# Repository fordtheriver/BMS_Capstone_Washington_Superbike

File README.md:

# BMS_Capstone_Washington_Superbike
This repository includes firmware, PCB design files and documentation to build the BMS for Washington Superbike. This BMS uses the TI MSP430F5529 microcontroller to interface with the LTC6811-1 Battery Stack Monitor. 

This code is written in C in Code Composer Studio. 

Current firmware is full of bugs and should be debugged by the end of June.

EAGLE PCB design files are included in the EAGLE folder

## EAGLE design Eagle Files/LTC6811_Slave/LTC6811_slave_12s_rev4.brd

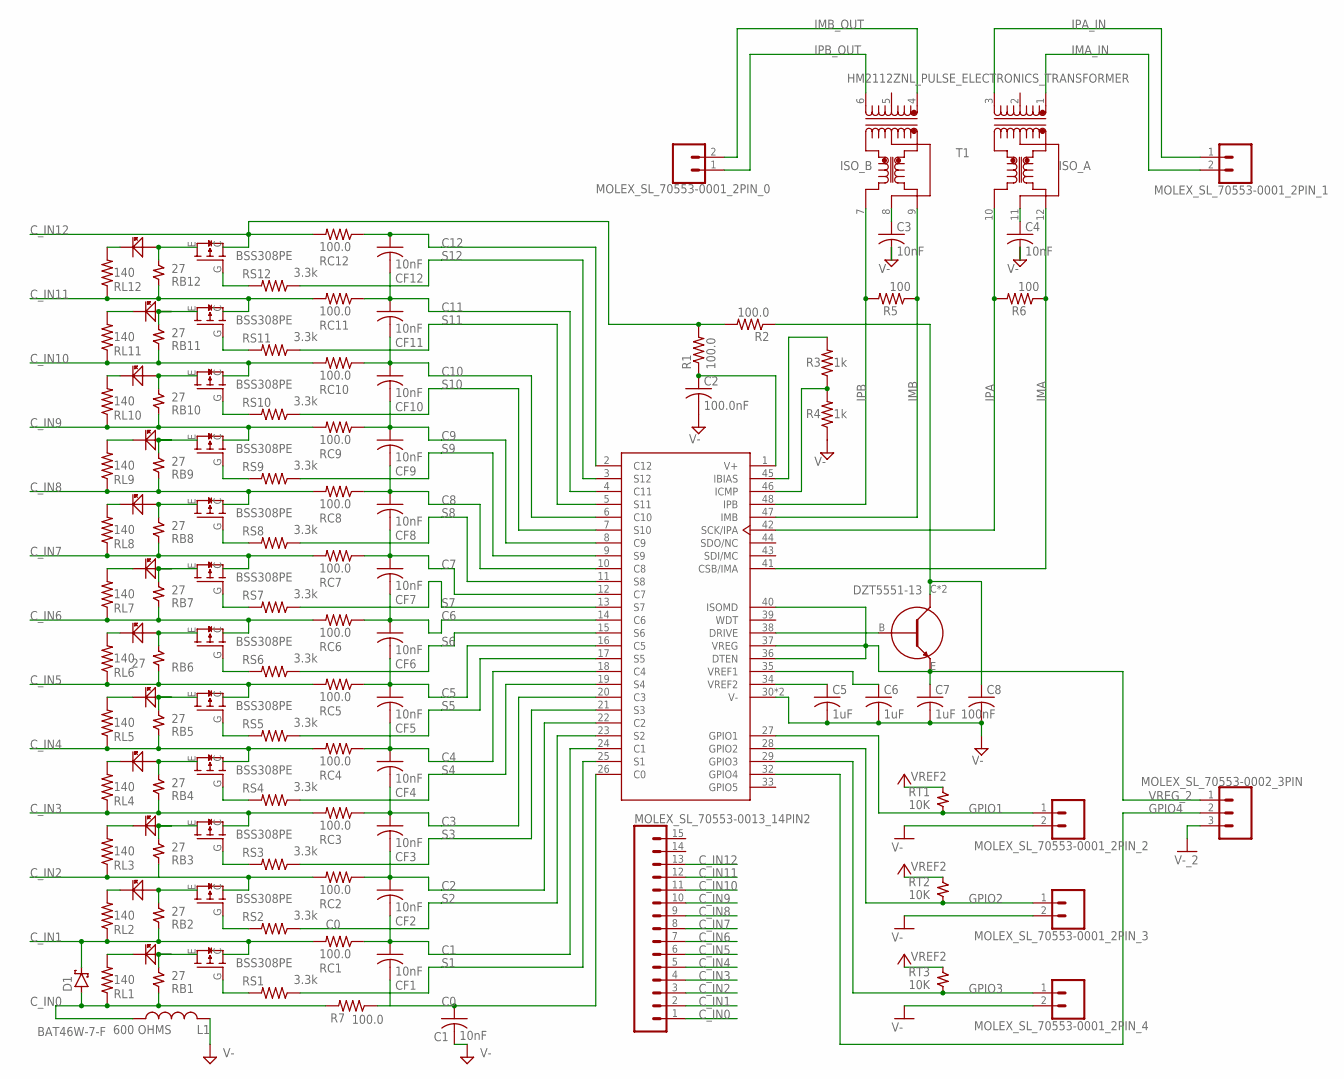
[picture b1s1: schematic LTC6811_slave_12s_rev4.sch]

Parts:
C1, C3, C4: 10nF; C0805
C2: 100.0nF; C0805
C5, C6, C7: 1uF; C0805
C8: 100nF; C0805
CF1, CF2, CF3, CF4, CF5, CF6, CF7, CF8, CF9, CF10, CF11, CF12: 10nF; C0805
D1: BAT46W-7-F; SOD123
L1: 600 OHMS; 0805_COMPONENT
LED1, LED2, LED3, LED4, LED5, LED6, LED7, LED8, LED9, LED10, LED11, LED12: LED_0805; 0805_COMPONENT
MOLEX_SL_70553-0001_2PIN_0, MOLEX_SL_70553-0001_2PIN_1, MOLEX_SL_70553-0001_2PIN_2, MOLEX_SL_70553-0001_2PIN_3, MOLEX_SL_70553-0001_2PIN_4: CONN_02; 1X02
MOLEX_SL_70553-0002_3PIN: CONN_03; 1X03
MOLEX_SL_70553-0013_14PIN2: CONN_15; 1X15
R1, R2, R7: 100.0; R0805
R3, R4: 1k; R0805
R5, R6: 100; R0805
RB1, RB2, RB3, RB4, RB5, RB6, RB7, RB8, RB9, RB10, RB11, RB12: 27; 2817_COMPONENT
RC1, RC2, RC3, RC4, RC5, RC6, RC7, RC8, RC9, RC10, RC11, RC12: 100.0; R0805
RL1, RL2, RL3, RL4, RL5, RL6, RL7, RL8, RL9, RL10, RL11, RL12: 140; R0805
RS1, RS2, RS3, RS4, RS5, RS6, RS7, RS8, RS9, RS10, RS11, RS12: 3.3k; R0805
RT1, RT2, RT3: 10K; 0805_RESISTOR
SW1, SW2, SW3, SW4, SW5, SW6, SW7, SW8, SW9, SW10, SW11, SW12: BSS308PEH6327; SOT23
SW13: DZT5551-13; SOT223-4
U1: LTC6811HG-2#PBF; LTC6811-1
U$3: HM2112ZNL_PULSE_ELECTRONICS_TRANSFORMER; HM2112ZNL_12SMT

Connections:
C0: C1.1, R7.1, U1.26 (C0)
C1: CF1.1, CF2.2, RC1.1, U1.24 (C1)
C2: CF2.1, CF3.2, RC2.1, U1.22 (C2)
C3: CF3.1, CF4.2, RC3.1, U1.20 (C3)
C4: CF4.1, CF5.2, RC4.1, U1.18 (C4)
C5: CF5.1, CF6.2, RC5.1, U1.16 (C5)
C6: CF6.1, CF7.2, RC6.1, U1.14 (C6)
C7: CF7.1, CF8.2, RC7.1, U1.12 (C7)
C8: CF8.1, CF9.2, RC8.1, U1.10 (C8)
C9: CF9.1, CF10.2, RC9.1, U1.8 (C9)
C10: CF10.1, CF11.2, RC10.1, U1.6 (C10)
C11: CF11.1, CF12.2, RC11.1, U1.4 (C11)
C12: CF12.1, RC12.1, U1.2 (C12)
C_IN0: D1.A, L1.1, MOLEX_SL_70553-0013_14PIN2.1, R7.2, RB1.2, RL1.1
C_IN1: D1.C, MOLEX_SL_70553-0013_14PIN2.2, RB2.2, RC1.2, RL2.1, SW1.C
C_IN2: MOLEX_SL_70553-0013_14PIN2.3, RB3.2, RC2.2, RL3.1, SW2.C
C_IN3: MOLEX_SL_70553-0013_14PIN2.4, RB4.2, RC3.2, RL4.1, SW3.C
C_IN4: MOLEX_SL_70553-0013_14PIN2.5, RB5.2, RC4.2, RL5.1, SW4.C
C_IN5: MOLEX_SL_70553-0013_14PIN2.6, RB6.2, RC5.2, RL6.1, SW5.C
C_IN6: MOLEX_SL_70553-0013_14PIN2.7, RB7.2, RC6.2, RL7.1, SW6.C
C_IN7: MOLEX_SL_70553-0013_14PIN2.8, RB8.2, RC7.2, RL8.1, SW7.C
C_IN8: MOLEX_SL_70553-0013_14PIN2.9, RB9.2, RC8.2, RL9.1, SW8.C
C_IN9: MOLEX_SL_70553-0013_14PIN2.10, RB10.2, RC9.2, RL10.1, SW9.C
C_IN10: MOLEX_SL_70553-0013_14PIN2.11, RB11.2, RC10.2, RL11.1, SW10.C
C_IN11: MOLEX_SL_70553-0013_14PIN2.12, RB12.2, RC11.2, RL12.1, SW11.C
C_IN12: MOLEX_SL_70553-0013_14PIN2.13, R1.2, R2.2, RC12.2, SW12.C
DRIVE_2: SW13.B, U1.38 (DRIVE)
GPIO1: MOLEX_SL_70553-0001_2PIN_2.1, RT1.P$2, U1.27 (GPIO1)
GPIO2: MOLEX_SL_70553-0001_2PIN_3.1, RT2.P$2, U1.28 (GPIO2)
GPIO3: MOLEX_SL_70553-0001_2PIN_4.1, RT3.P$2, U1.29 (GPIO3)
GPIO4: MOLEX_SL_70553-0002_3PIN.2, U1.32 (GPIO4)
IBIAS_2: R3.2, U1.45 (IBIAS)
ICMP_2: R3.1, R4.2, U1.46 (ICMP)
IMA: R6.1, U1.41 (CSB/IMA), U$3.12
IMA_IN: MOLEX_SL_70553-0001_2PIN_1.2, U$3.1
IMB: R5.1, U1.47 (IMB), U$3.9
IMB_OUT: MOLEX_SL_70553-0001_2PIN_0.2, U$3.4
IPA: R6.2, U1.42 (SCK/IPA), U$3.10
IPA_IN: MOLEX_SL_70553-0001_2PIN_1.1, U$3.3
IPB: R5.2, U1.48 (IPB), U$3.7
IPB_OUT: MOLEX_SL_70553-0001_2PIN_0.1, U$3.6
unnamed: C2.1, R1.1, U1.1 (V+)
unnamed: C3.1, U$3.8
unnamed: C4.1, U$3.11
unnamed: LED1.2, RB1.1, SW1.E
unnamed: RS1.2, SW1.G (B)
unnamed: LED1.1, RL1.2
unnamed: LED2.2, RB2.1, SW2.E
unnamed: RS2.2, SW2.G (B)
unnamed: LED2.1, RL2.2
unnamed: LED3.2, RB3.1, SW3.E
unnamed: RS3.2, SW3.G (B)
unnamed: LED3.1, RL3.2
unnamed: LED4.2, RB4.1, SW4.E
unnamed: RS4.2, SW4.G (B)
unnamed: LED4.1, RL4.2
unnamed: LED5.2, RB5.1, SW5.E
unnamed: RS5.2, SW5.G (B)
unnamed: LED5.1, RL5.2
unnamed: LED6.2, RB6.1, SW6.E
unnamed: RS6.2, SW6.G (B)
unnamed: LED6.1, RL6.2
unnamed: LED7.2, RB7.1, SW7.E
unnamed: RS7.2, SW7.G (B)
unnamed: LED7.1, RL7.2
unnamed: LED8.2, RB8.1, SW8.E
unnamed: RS8.2, SW8.G (B)
unnamed: LED8.1, RL8.2
unnamed: LED9.2, RB9.1, SW9.E
unnamed: RS9.2, SW9.G (B)
unnamed: LED9.1, RL9.2
unnamed: LED10.2, RB10.1, SW10.E
unnamed: RS10.2, SW10.G (B)
unnamed: LED10.1, RL10.2
unnamed: LED11.2, RB11.1, SW11.E
unnamed: RS11.2, SW11.G (B)
unnamed: LED11.1, RL11.2
unnamed: LED12.2, RB12.1, SW12.E
unnamed: RS12.2, SW12.G (B)
unnamed: LED12.1, RL12.2
S1: RS1.1, U1.25 (S1)
S2: RS2.1, U1.23 (S2)
S3: RS3.1, U1.21 (S3)
S4: RS4.1, U1.19 (S4)
S5: RS5.1, U1.17 (S5)
S6: RS6.1, U1.15 (S6)
S7: RS7.1, U1.13 (S7)
S8: RS8.1, U1.11 (S8)
S9: RS9.1, U1.9 (S9)
S10: RS10.1, U1.7 (S10)
S11: RS11.1, U1.5 (S11)
S12: RS12.1, U1.3 (S12)
V-: C1.2, C2.2, C3.2, C4.2, C5.2, C6.2, C7.2, C8.2, L1.2, MOLEX_SL_70553-0001_2PIN_2.2, MOLEX_SL_70553-0001_2PIN_3.2, MOLEX_SL_70553-0001_2PIN_4.2, MOLEX_SL_70553-0002_3PIN.3, R4.1, U1.30 (V-), U1.31 (V-)
VREF1_C4_2: C6.1, U1.35 (VREF1)
VREF2_C5_2: C5.1, RT1.P$1, RT2.P$1, RT3.P$1, U1.34 (VREF2)
VREG_2: C7.1, MOLEX_SL_70553-0002_3PIN.1, SW13.E, U1.36 (DTEN), U1.37 (VREG), U1.40 (ISOMD)
VREG_CAP_2: C8.1, R2.1, SW13.C, SW13.C@2 (C)

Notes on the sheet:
ISO_B
ISO_A
DZT5551-13

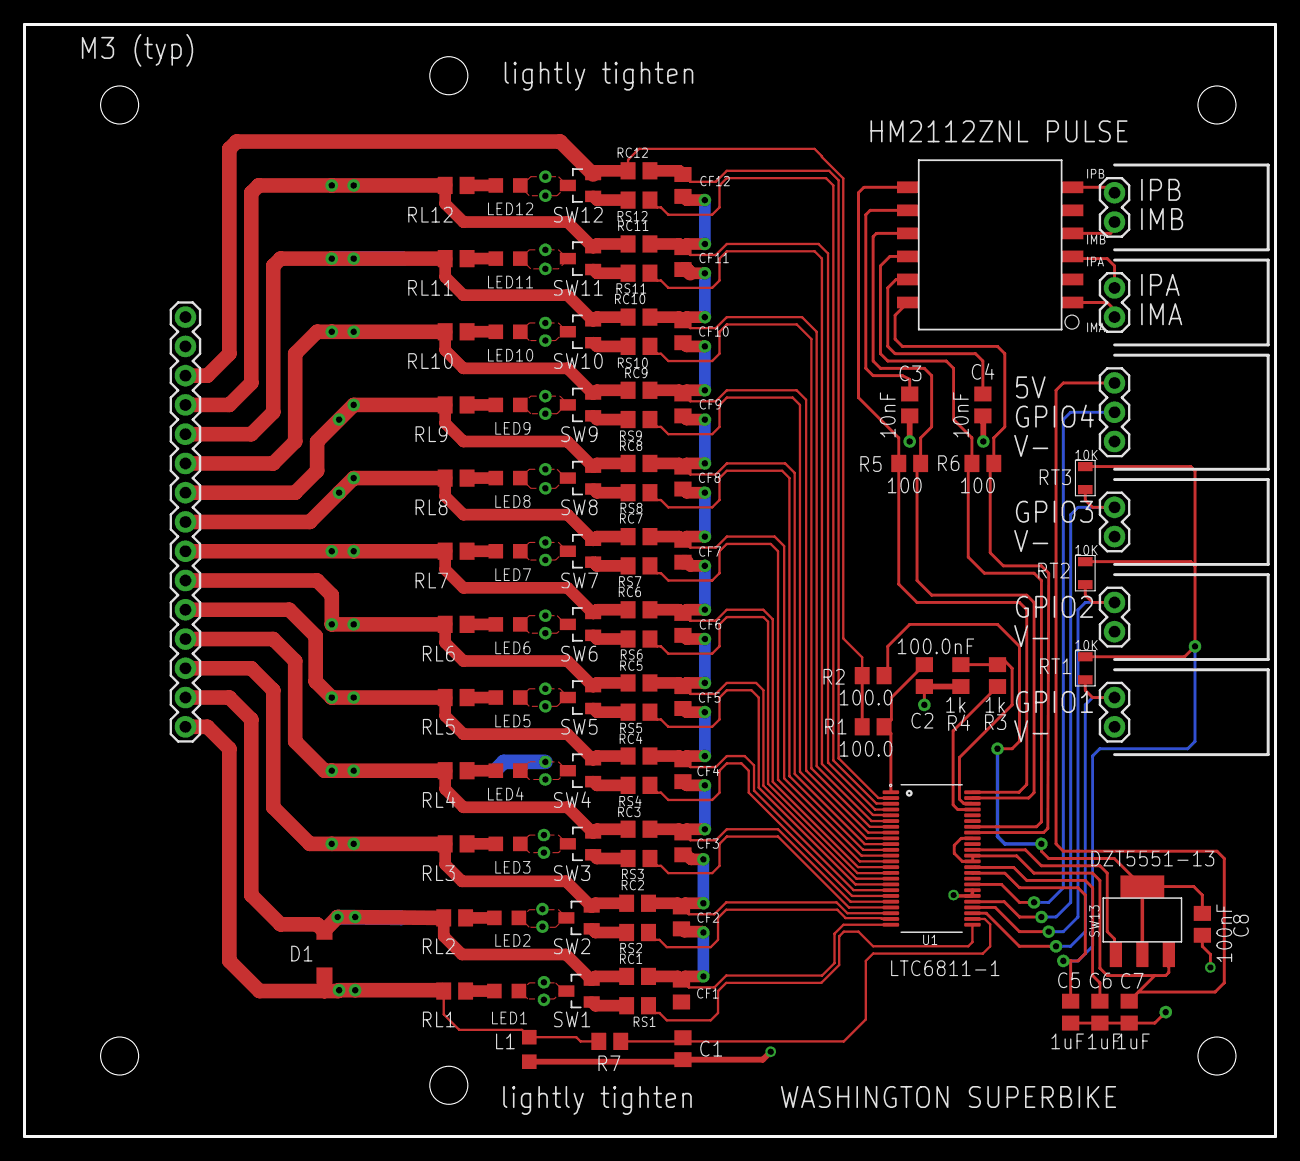
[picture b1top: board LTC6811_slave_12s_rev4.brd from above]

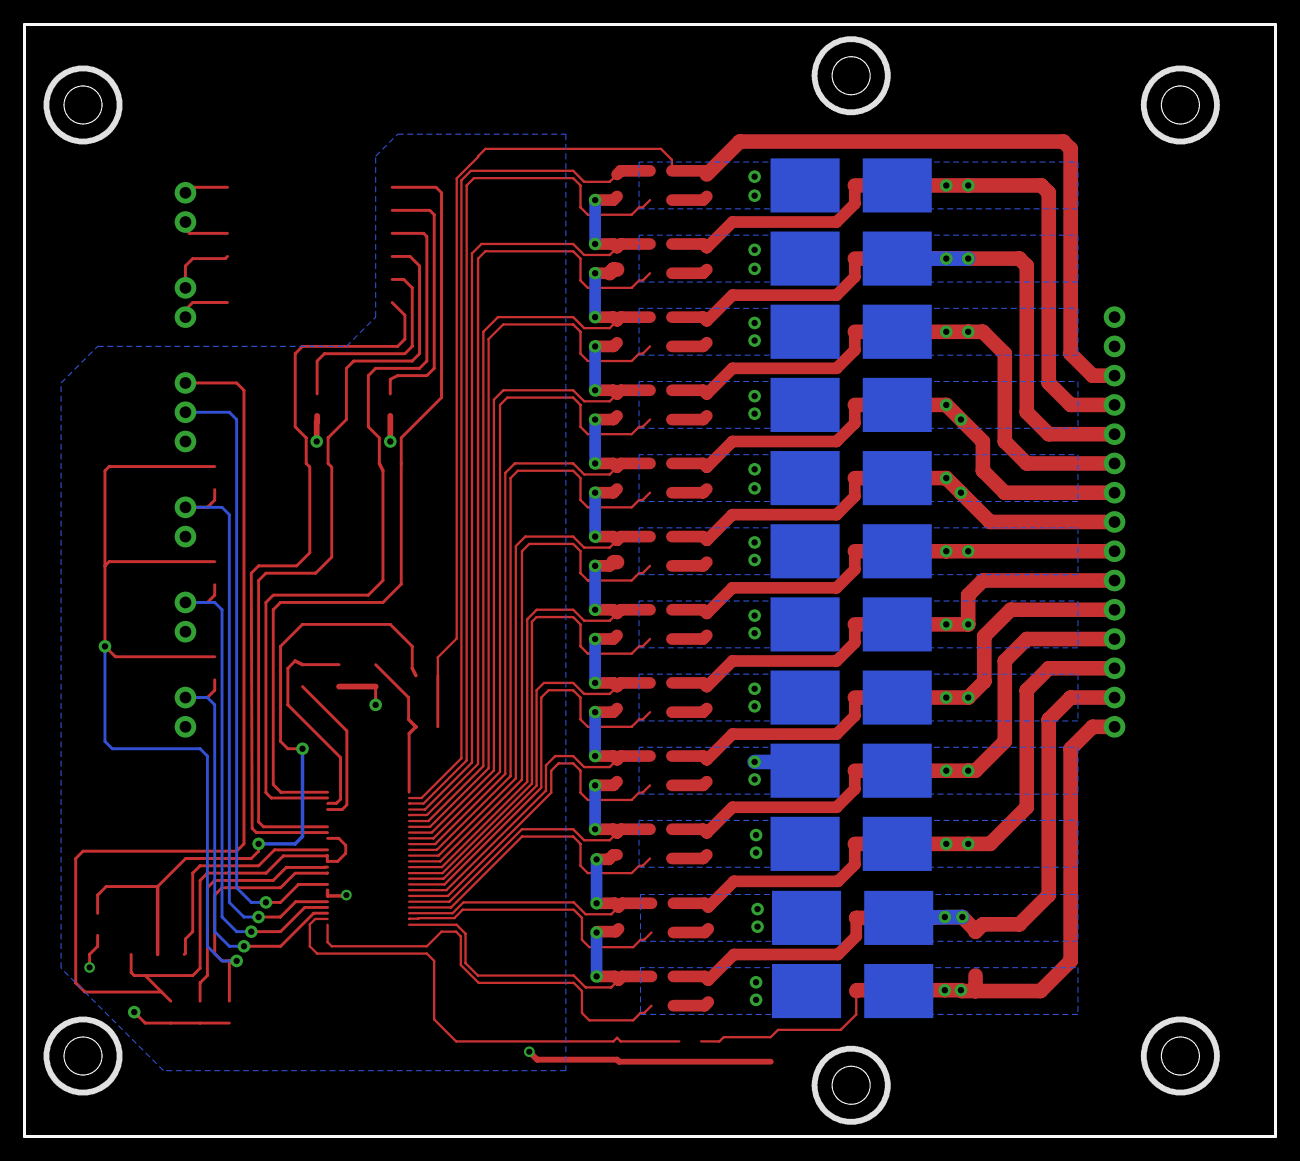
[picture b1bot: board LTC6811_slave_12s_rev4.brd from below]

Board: 2 copper layers, 108.6 x 96.5 mm, 114 parts (12 on the bottom side), 97 nets.

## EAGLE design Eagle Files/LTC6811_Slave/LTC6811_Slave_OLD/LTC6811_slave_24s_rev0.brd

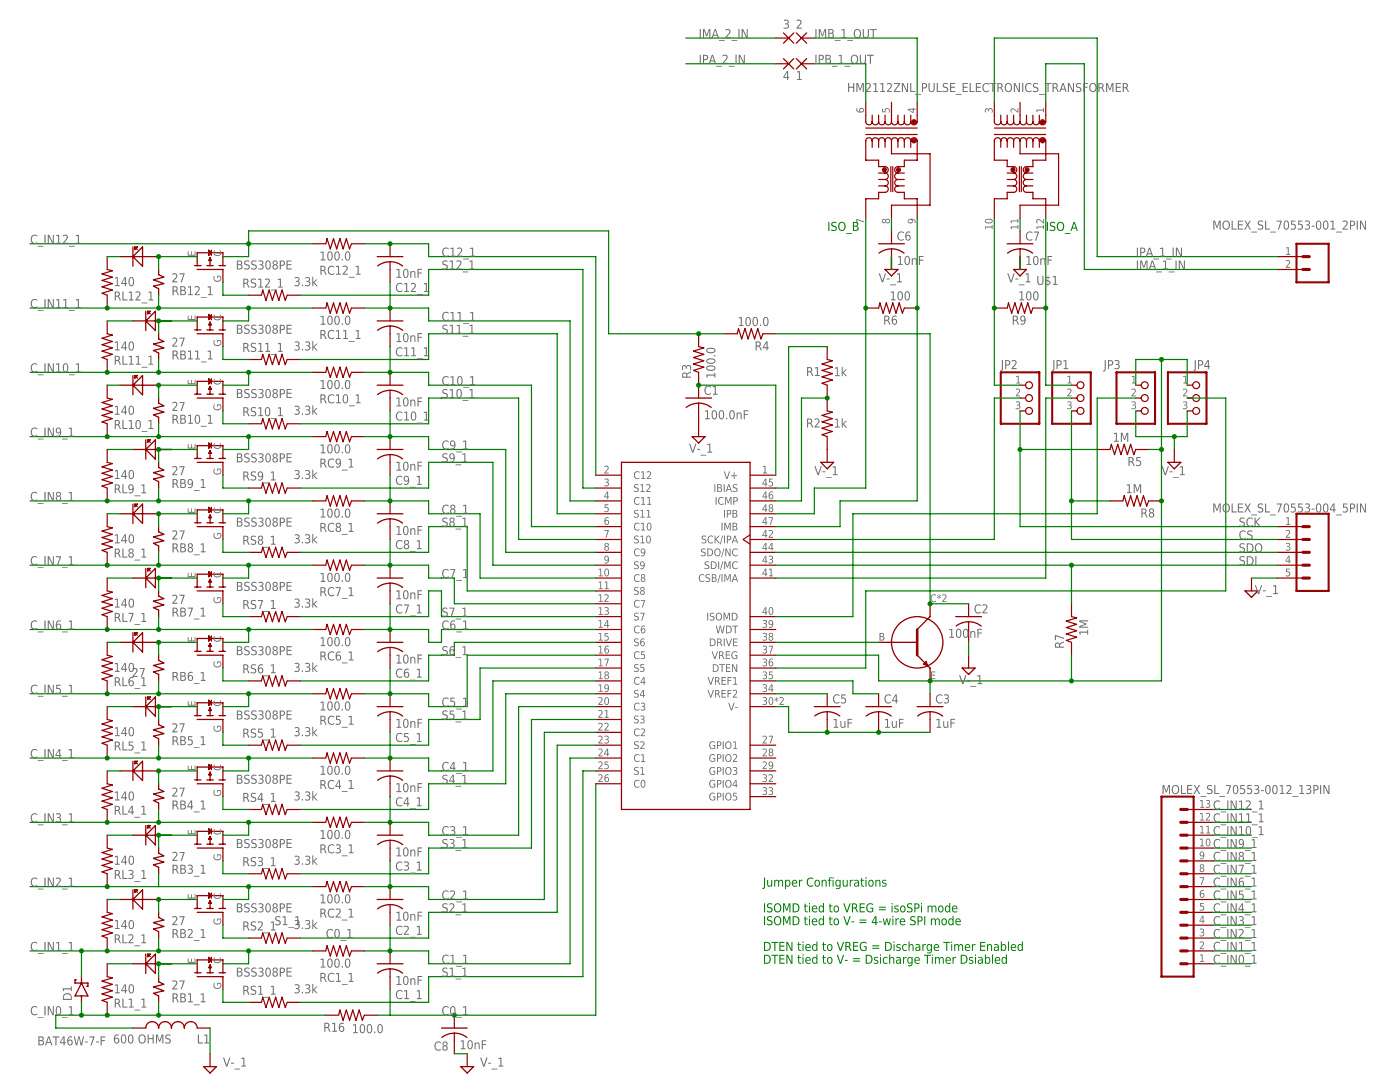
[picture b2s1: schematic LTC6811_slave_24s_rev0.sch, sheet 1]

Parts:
1, 2, 3, 4: WIREPAD2,15/1,0; 2,15/1,0
C1: 100.0nF; C0805
C1_1, C2_1, C3_1, C4_1, C5_1, C6, C6_1, C7, C7_1, C8, C8_1, C9_1, C10_1, C11_1, C12_1: 10nF; C0805
C2: 100nF; C0805
C3, C4, C5: 1uF; C0805
D1: BAT46W-7-F; SOD123
DZT5551-13: DZT5551-13; SOT223-4
JP1, JP2, JP3, JP4: PINHD-1X3; 1X03
L1: 600 OHMS; 0805_COMPONENT
LED1_3, LED1_4, LED1_5, LED1_6, LED1_7, LED1_8, LED1_9, LED1_10, LED1_11, LED1_12, LED1_13, LED1_14: LED_0805; 0805_COMPONENT
MOLEX_SL_70553-001_2PIN: CONN_02; 1X02
MOLEX_SL_70553-004_5PIN: CONN_05; 1X05
MOLEX_SL_70553-0012_13PIN: CONN_13; 1X13
R1, R2: 1k; R0805
R3, R4, R16: 100.0; R0805
R5, R7, R8: 1M; R0805
R6, R9: 100; R0805
RB1_1, RB2_1, RB3_1, RB4_1, RB5_1, RB6_1, RB7_1, RB8_1, RB9_1, RB10_1, RB11_1, RB12_1: 27; 2817_COMPONENT
RC1_1, RC2_1, RC3_1, RC4_1, RC5_1, RC6_1, RC7_1, RC8_1, RC9_1, RC10_1, RC11_1, RC12_1: 100.0; R0805
RL1_1, RL2_1, RL3_1, RL4_1, RL5_1, RL6_1, RL7_1, RL8_1, RL9_1, RL10_1, RL11_1, RL12_1: 140; R0805
RS1_1, RS2_1, RS3_1, RS4_1, RS5_1, RS6_1, RS7_1, RS8_1, RS9_1, RS10_1, RS11_1, RS12_1: 3.3k; R0805
T1_3, T1_4, T1_5, T1_6, T1_7, T1_8, T1_9, T1_10, T1_11, T1_12, T1_13, T1_14: BSS308PEH6327; SOT23
U1: LTC6811HG-2#PBF; LTC6811-1
U$1: HM2112ZNL_PULSE_ELECTRONICS_TRANSFORMER; HM2112ZNL_12SMT

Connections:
C0_1: C8.1, R16.1, U1.26 (C0)
C1_1: C1_1.1, C2_1.2, RC1_1.1, U1.24 (C1)
C2_1: C2_1.1, C3_1.2, RC2_1.1, U1.22 (C2)
C3_1: C3_1.1, C4_1.2, RC3_1.1, U1.20 (C3)
C4_1: C4_1.1, C5_1.2, RC4_1.1, U1.18 (C4)
C5_1: C5_1.1, C6_1.2, RC5_1.1, U1.16 (C5)
C6_1: C6_1.1, C7_1.2, RC6_1.1, U1.14 (C6)
C7_1: C7_1.1, C8_1.2, RC7_1.1, U1.12 (C7)
C8_1: C8_1.1, C9_1.2, RC8_1.1, U1.10 (C8)
C9_1: C9_1.1, C10_1.2, RC9_1.1, U1.8 (C9)
C10_1: C10_1.1, C11_1.2, RC10_1.1, U1.6 (C10)
C11_1: C11_1.1, C12_1.2, RC11_1.1, U1.4 (C11)
C12_1: C12_1.1, RC12_1.1, U1.2 (C12)
CS: JP1.3, MOLEX_SL_70553-004_5PIN.2, R8.2
CS_OR_IMA: JP1.2, U1.41 (CSB/IMA)
C_IN0_1: D1.A, L1.1, MOLEX_SL_70553-0012_13PIN.1, R16.2, RB1_1.2, RL1_1.1
C_IN1_1: D1.C, MOLEX_SL_70553-0012_13PIN.2, RB2_1.2, RC1_1.2, RL2_1.1, T1_3.C
C_IN2_1: MOLEX_SL_70553-0012_13PIN.3, RB3_1.2, RC2_1.2, RL3_1.1, T1_4.C
C_IN3_1: MOLEX_SL_70553-0012_13PIN.4, RB4_1.2, RC3_1.2, RL4_1.1, T1_7.C
C_IN4_1: MOLEX_SL_70553-0012_13PIN.5, RB5_1.2, RC4_1.2, RL5_1.1, T1_8.C
C_IN5_1: MOLEX_SL_70553-0012_13PIN.6, RB6_1.2, RC5_1.2, RL6_1.1, T1_5.C
C_IN6_1: MOLEX_SL_70553-0012_13PIN.7, RB7_1.2, RC6_1.2, RL7_1.1, T1_6.C
C_IN7_1: MOLEX_SL_70553-0012_13PIN.8, RB8_1.2, RC7_1.2, RL8_1.1, T1_9.C
C_IN8_1: MOLEX_SL_70553-0012_13PIN.9, RB9_1.2, RC8_1.2, RL9_1.1, T1_10.C
C_IN9_1: MOLEX_SL_70553-0012_13PIN.10, RB10_1.2, RC9_1.2, RL10_1.1, T1_11.C
C_IN10_1: MOLEX_SL_70553-0012_13PIN.11, RB11_1.2, RC10_1.2, RL11_1.1, T1_12.C
C_IN11_1: MOLEX_SL_70553-0012_13PIN.12, RB12_1.2, RC11_1.2, RL12_1.1, T1_13.C
C_IN12_1: MOLEX_SL_70553-0012_13PIN.13, R3.2, R4.2, RC12_1.2, T1_14.C
DRIVE: DZT5551-13.B, U1.38 (DRIVE)
DTEN: JP4.2, U1.36 (DTEN)
IBIAS: R1.2, U1.45 (IBIAS)
ICMP: R1.1, R2.2, U1.46 (ICMP)
IMA_1_IN: MOLEX_SL_70553-001_2PIN.2, U$1.1
IMA_2_IN: 3.1; also elsewhere on the board
IMB: R6.1, U1.47 (IMB), U$1.9
IMB_1_OUT: 2.1, U$1.4
IPA_1_IN: MOLEX_SL_70553-001_2PIN.1, U$1.3
IPA_2_IN: 4.1; also elsewhere on the board
IPB: R6.2, U1.48 (IPB), U$1.7
IPB_1_OUT: 1.1, U$1.6
ISOMD: JP3.2, U1.40 (ISOMD)
unnamed: C6.1, U$1.8
unnamed: C1.1, R3.1, U1.1 (V+)
unnamed: JP2.1, R9.2, U$1.10
unnamed: JP1.1, R9.1, U$1.12
unnamed: C7.1, U$1.11
unnamed: LED1_11.2, RB9_1.1, T1_11.E
unnamed: RS9_1.2, T1_11.G (B)
unnamed: LED1_11.1, RL9_1.2
unnamed: LED1_12.2, RB10_1.1, T1_12.E
unnamed: RS10_1.2, T1_12.G (B)
unnamed: LED1_12.1, RL10_1.2
unnamed: LED1_13.2, RB11_1.1, T1_13.E
unnamed: LED1_3.2, RB1_1.1, T1_3.E
unnamed: RS1_1.2, T1_3.G (B)
unnamed: LED1_3.1, RL1_1.2
unnamed: LED1_4.2, RB2_1.1, T1_4.E
unnamed: RS2_1.2, T1_4.G (B)
unnamed: LED1_4.1, RL2_1.2
unnamed: LED1_5.2, RB5_1.1, T1_5.E
unnamed: RS5_1.2, T1_5.G (B)
unnamed: LED1_5.1, RL5_1.2
unnamed: LED1_6.2, RB6_1.1, T1_6.E
unnamed: RS6_1.2, T1_6.G (B)
unnamed: LED1_6.1, RL6_1.2
unnamed: LED1_9.2, RB7_1.1, T1_9.E
unnamed: LED1_7.2, RB3_1.1, T1_7.E
unnamed: RS3_1.2, T1_7.G (B)
unnamed: LED1_7.1, RL3_1.2
unnamed: LED1_8.2, RB4_1.1, T1_8.E
unnamed: RS4_1.2, T1_8.G (B)
unnamed: LED1_8.1, RL4_1.2
unnamed: RS11_1.2, T1_13.G (B)
unnamed: RS7_1.2, T1_9.G (B)
unnamed: LED1_9.1, RL7_1.2
unnamed: LED1_10.2, RB8_1.1, T1_10.E
unnamed: RS8_1.2, T1_10.G (B)
unnamed: LED1_10.1, RL8_1.2
unnamed: LED1_13.1, RL11_1.2
unnamed: LED1_14.2, RB12_1.1, T1_14.E
unnamed: RS12_1.2, T1_14.G (B)
unnamed: LED1_14.1, RL12_1.2
S1_1: RS1_1.1, U1.25 (S1)
S2_1: RS2_1.1, U1.23 (S2)
S3_1: RS3_1.1, U1.21 (S3)
S4_1: RS4_1.1, U1.19 (S4)
S5_1: RS5_1.1, U1.17 (S5)
S6_1: RS6_1.1, U1.15 (S6)
S7_1: RS7_1.1, U1.13 (S7)
S8_1: RS8_1.1, U1.11 (S8)
S9_1: RS9_1.1, U1.9 (S9)
S10_1: RS10_1.1, U1.7 (S10)
S11_1: RS11_1.1, U1.5 (S11)
S12_1: RS12_1.1, U1.3 (S12)
SCK: JP2.3, MOLEX_SL_70553-004_5PIN.1, R5.2
SCK_OR_IPA: JP2.2, U1.42 (SCK/IPA)
SDI: MOLEX_SL_70553-004_5PIN.4, R7.2, U1.43 (SDI/MC)
SDO: MOLEX_SL_70553-004_5PIN.3, U1.44 (SDO/NC)
V-_1: C1.2, C2.2, C3.2, C4.2, C5.2, C6.2, C7.2, C8.2, JP3.3, JP4.3, L1.2, MOLEX_SL_70553-004_5PIN.5, R2.1, U1.30 (V-), U1.31 (V-)
VREF1_C4: C4.1, U1.35 (VREF1)
VREF2_C5: C5.1, U1.34 (VREF2)
VREG: C3.1, DZT5551-13.E, JP3.1, JP4.1, R5.1, R7.1, R8.1, U1.37 (VREG)
VREG_CAP: C2.1, DZT5551-13.C, DZT5551-13.C@2 (C), R4.1

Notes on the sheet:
ISO_B
ISO_A
ISOMD tied to VREG = isoSPi mode
ISOMD tied to V- = 4-wire SPI mode
DTEN tied to VREG = Discharge Timer Enabled
DTEN tied to V- = Dsicharge Timer Dsiabled
Jumper Configurations

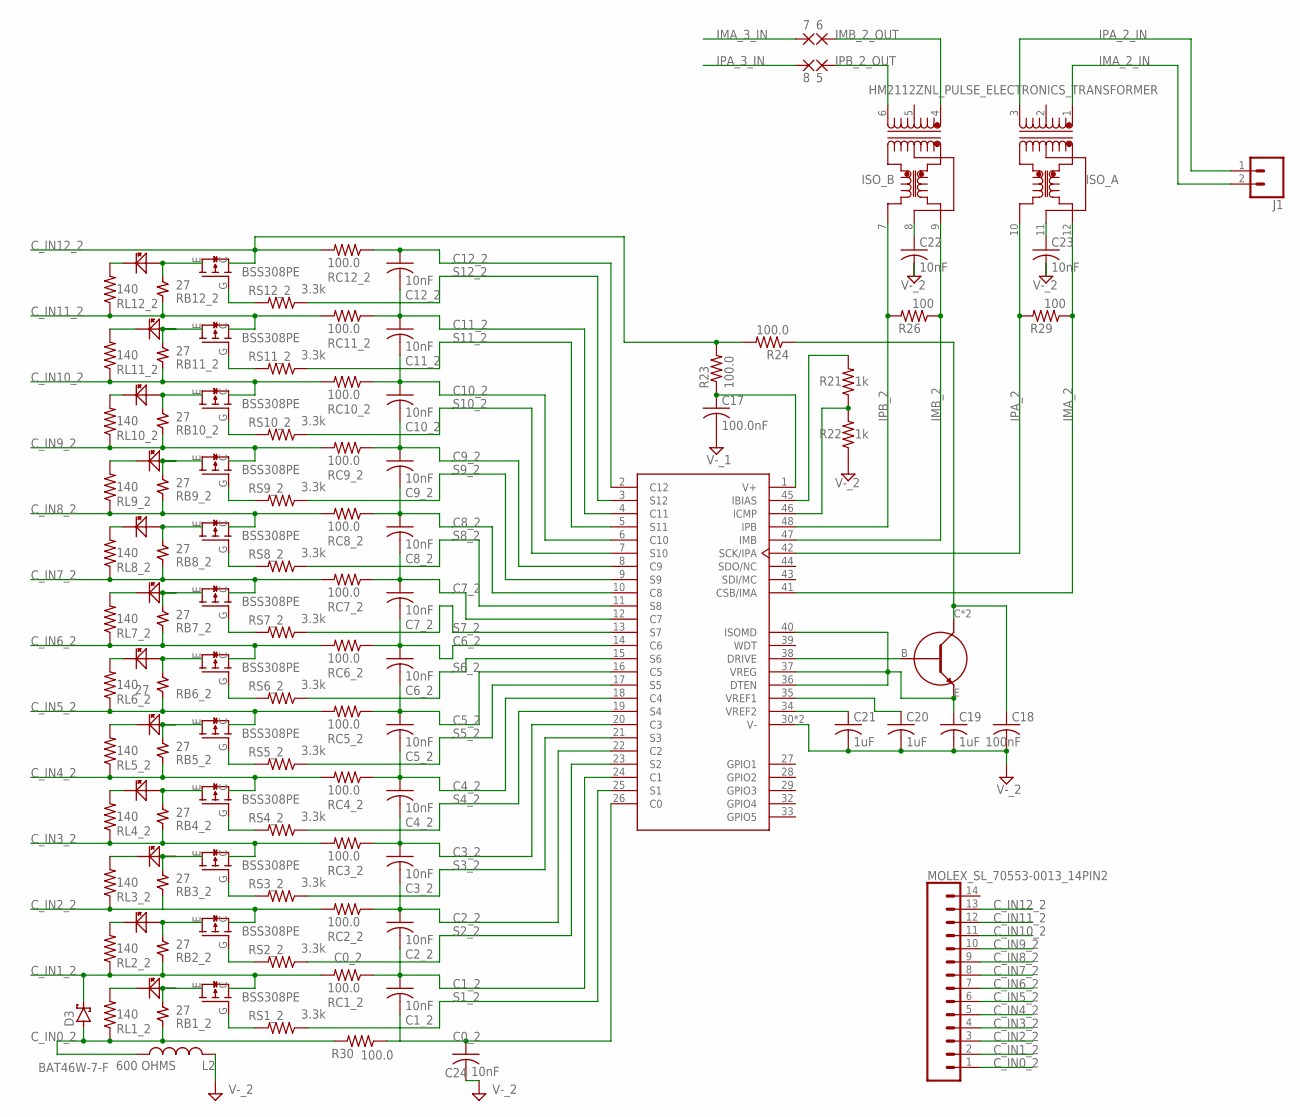
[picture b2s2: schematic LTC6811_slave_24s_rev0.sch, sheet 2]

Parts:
5, 6, 7, 8: WIREPAD2,15/1,0; 2,15/1,0
C1_2, C2_2, C3_2, C4_2, C5_2, C6_2, C7_2, C8_2, C9_2, C10_2, C11_2, C12_2, C22, C23, C24: 10nF; C0805
C17: 100.0nF; C0805
C18: 100nF; C0805
C19, C20, C21: 1uF; C0805
D3: BAT46W-7-F; SOD123
DZT5551-2: DZT5551-13; SOT223-4
J1: CONN_02; 1X02
L2: 600 OHMS; 0805_COMPONENT
LED1_25, LED1_26, LED1_27, LED1_28, LED1_29, LED1_30, LED1_31, LED1_32, LED1_33, LED1_34, LED1_35, LED1_36: LED_0805; 0805_COMPONENT
MOLEX_SL_70553-0013_14PIN2: CONN_14; 1X14
R21, R22: 1k; R0805
R23, R24, R30: 100.0; R0805
R26, R29: 100; R0805
RB1_2, RB2_2, RB3_2, RB4_2, RB5_2, RB6_2, RB7_2, RB8_2, RB9_2, RB10_2, RB11_2, RB12_2: 27; 2817_COMPONENT
RC1_2, RC2_2, RC3_2, RC4_2, RC5_2, RC6_2, RC7_2, RC8_2, RC9_2, RC10_2, RC11_2, RC12_2: 100.0; R0805
RL1_2, RL2_2, RL3_2, RL4_2, RL5_2, RL6_2, RL7_2, RL8_2, RL9_2, RL10_2, RL11_2, RL12_2: 140; R0805
RS1_2, RS2_2, RS3_2, RS4_2, RS5_2, RS6_2, RS7_2, RS8_2, RS9_2, RS10_2, RS11_2, RS12_2: 3.3k; R0805
T1_25, T1_26, T1_27, T1_28, T1_29, T1_30, T1_31, T1_32, T1_33, T1_34, T1_35, T1_36: BSS308PEH6327; SOT23
U3: LTC6811HG-2#PBF; LTC6811-1
U$3: HM2112ZNL_PULSE_ELECTRONICS_TRANSFORMER; HM2112ZNL_12SMT

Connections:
C0_2: C24.1, R30.1, U3.26 (C0)
C1_2: C1_2.1, C2_2.2, RC1_2.1, U3.24 (C1)
C2_2: C2_2.1, C3_2.2, RC2_2.1, U3.22 (C2)
C3_2: C3_2.1, C4_2.2, RC3_2.1, U3.20 (C3)
C4_2: C4_2.1, C5_2.2, RC4_2.1, U3.18 (C4)
C5_2: C5_2.1, C6_2.2, RC5_2.1, U3.16 (C5)
C6_2: C6_2.1, C7_2.2, RC6_2.1, U3.14 (C6)
C7_2: C7_2.1, C8_2.2, RC7_2.1, U3.12 (C7)
C8_2: C8_2.1, C9_2.2, RC8_2.1, U3.10 (C8)
C9_2: C9_2.1, C10_2.2, RC9_2.1, U3.8 (C9)
C10_2: C10_2.1, C11_2.2, RC10_2.1, U3.6 (C10)
C11_2: C11_2.1, C12_2.2, RC11_2.1, U3.4 (C11)
C12_2: C12_2.1, RC12_2.1, U3.2 (C12)
C_IN0_2: D3.A, L2.1, MOLEX_SL_70553-0013_14PIN2.1, R30.2, RB1_2.2, RL1_2.1
C_IN1_2: D3.C, MOLEX_SL_70553-0013_14PIN2.2, RB2_2.2, RC1_2.2, RL2_2.1, T1_25.C
C_IN2_2: MOLEX_SL_70553-0013_14PIN2.3, RB3_2.2, RC2_2.2, RL3_2.1, T1_26.C
C_IN3_2: MOLEX_SL_70553-0013_14PIN2.4, RB4_2.2, RC3_2.2, RL4_2.1, T1_27.C
C_IN4_2: MOLEX_SL_70553-0013_14PIN2.5, RB5_2.2, RC4_2.2, RL5_2.1, T1_28.C
C_IN5_2: MOLEX_SL_70553-0013_14PIN2.6, RB6_2.2, RC5_2.2, RL6_2.1, T1_29.C
C_IN6_2: MOLEX_SL_70553-0013_14PIN2.7, RB7_2.2, RC6_2.2, RL7_2.1, T1_30.C
C_IN7_2: MOLEX_SL_70553-0013_14PIN2.8, RB8_2.2, RC7_2.2, RL8_2.1, T1_31.C
C_IN8_2: MOLEX_SL_70553-0013_14PIN2.9, RB9_2.2, RC8_2.2, RL9_2.1, T1_32.C
C_IN9_2: MOLEX_SL_70553-0013_14PIN2.10, RB10_2.2, RC9_2.2, RL10_2.1, T1_33.C
C_IN10_2: MOLEX_SL_70553-0013_14PIN2.11, RB11_2.2, RC10_2.2, RL11_2.1, T1_34.C
C_IN11_2: MOLEX_SL_70553-0013_14PIN2.12, RB12_2.2, RC11_2.2, RL12_2.1, T1_35.C
C_IN12_2: MOLEX_SL_70553-0013_14PIN2.13, R23.2, R24.2, RC12_2.2, T1_36.C
DRIVE_2: DZT5551-2.B, U3.38 (DRIVE)
IBIAS_2: R21.2, U3.45 (IBIAS)
ICMP_2: R21.1, R22.2, U3.46 (ICMP)
IMA_2: R29.1, U3.41 (CSB/IMA), U$3.12
IMA_2_IN: J1.2, U$3.1; also elsewhere on the board
IMA_3_IN: 7.1
IMB_2: R26.1, U3.47 (IMB), U$3.9
IMB_2_OUT: 6.1, U$3.4
IPA_2: R29.2, U3.42 (SCK/IPA), U$3.10
IPA_2_IN: J1.1, U$3.3; also elsewhere on the board
IPA_3_IN: 8.1
IPB_2: R26.2, U3.48 (IPB), U$3.7
IPB_2_OUT: 5.1, U$3.6
unnamed: C17.1, R23.1, U3.1 (V+)
unnamed: C22.1, U$3.8
unnamed: C23.1, U$3.11
unnamed: LED1_25.2, RB1_2.1, T1_25.E
unnamed: RS1_2.2, T1_25.G (B)
unnamed: LED1_25.1, RL1_2.2
unnamed: LED1_26.2, RB2_2.1, T1_26.E
unnamed: RS2_2.2, T1_26.G (B)
unnamed: LED1_26.1, RL2_2.2
unnamed: LED1_27.2, RB3_2.1, T1_27.E
unnamed: RS3_2.2, T1_27.G (B)
unnamed: LED1_27.1, RL3_2.2
unnamed: LED1_28.2, RB4_2.1, T1_28.E
unnamed: RS4_2.2, T1_28.G (B)
unnamed: LED1_28.1, RL4_2.2
unnamed: LED1_29.2, RB5_2.1, T1_29.E
unnamed: RS5_2.2, T1_29.G (B)
unnamed: LED1_29.1, RL5_2.2
unnamed: LED1_30.2, RB6_2.1, T1_30.E
unnamed: RS6_2.2, T1_30.G (B)
unnamed: LED1_30.1, RL6_2.2
unnamed: LED1_31.2, RB7_2.1, T1_31.E
unnamed: RS7_2.2, T1_31.G (B)
unnamed: LED1_31.1, RL7_2.2
unnamed: LED1_32.2, RB8_2.1, T1_32.E
unnamed: RS8_2.2, T1_32.G (B)
unnamed: LED1_32.1, RL8_2.2
unnamed: LED1_33.2, RB9_2.1, T1_33.E
unnamed: RS9_2.2, T1_33.G (B)
unnamed: LED1_33.1, RL9_2.2
unnamed: LED1_34.2, RB10_2.1, T1_34.E
unnamed: RS10_2.2, T1_34.G (B)
unnamed: LED1_34.1, RL10_2.2
unnamed: LED1_35.2, RB11_2.1, T1_35.E
unnamed: RS11_2.2, T1_35.G (B)
unnamed: LED1_35.1, RL11_2.2
unnamed: LED1_36.2, RB12_2.1, T1_36.E
unnamed: RS12_2.2, T1_36.G (B)
unnamed: LED1_36.1, RL12_2.2
S1_2: RS1_2.1, U3.25 (S1)
S2_2: RS2_2.1, U3.23 (S2)
S3_2: RS3_2.1, U3.21 (S3)
S4_2: RS4_2.1, U3.19 (S4)
S5_2: RS5_2.1, U3.17 (S5)
S6_2: RS6_2.1, U3.15 (S6)
S7_2: RS7_2.1, U3.13 (S7)
S8_2: RS8_2.1, U3.11 (S8)
S9_2: RS9_2.1, U3.9 (S9)
S10_2: RS10_2.1, U3.7 (S10)
S11_2: RS11_2.1, U3.5 (S11)
S12_2: RS12_2.1, U3.3 (S12)
V-_2: C17.2, C18.2, C19.2, C20.2, C21.2, C22.2, C23.2, C24.2, L2.2, R22.1, U3.30 (V-), U3.31 (V-)
VREF1_C4_2: C20.1, U3.35 (VREF1)
VREF2_C5_2: C21.1, U3.34 (VREF2)
VREG_2: C19.1, DZT5551-2.E, U3.36 (DTEN), U3.37 (VREG), U3.40 (ISOMD)
VREG_CAP_2: C18.1, DZT5551-2.C, DZT5551-2.C@2 (C), R24.1

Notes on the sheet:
ISO_B
ISO_A

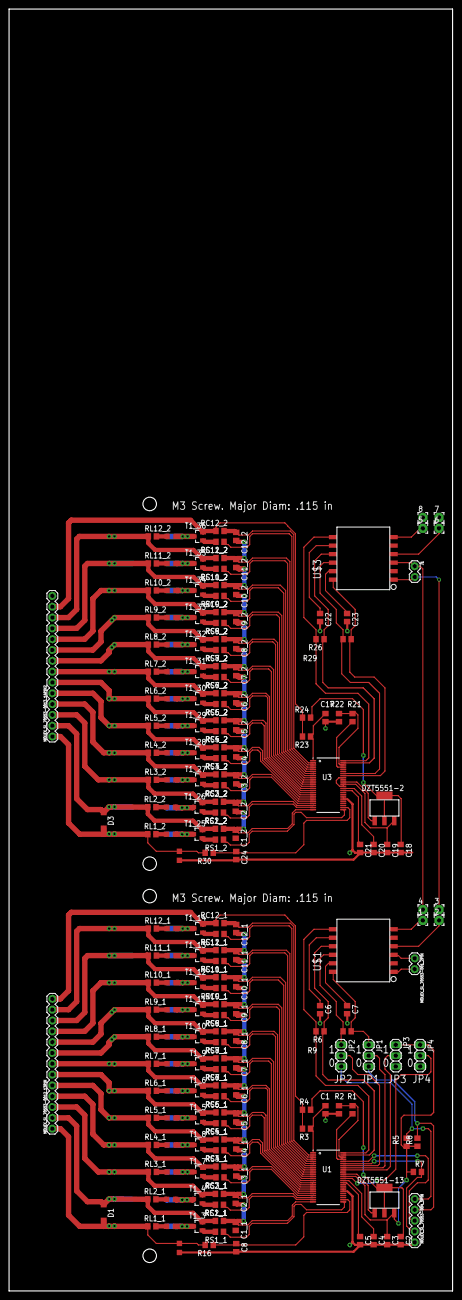
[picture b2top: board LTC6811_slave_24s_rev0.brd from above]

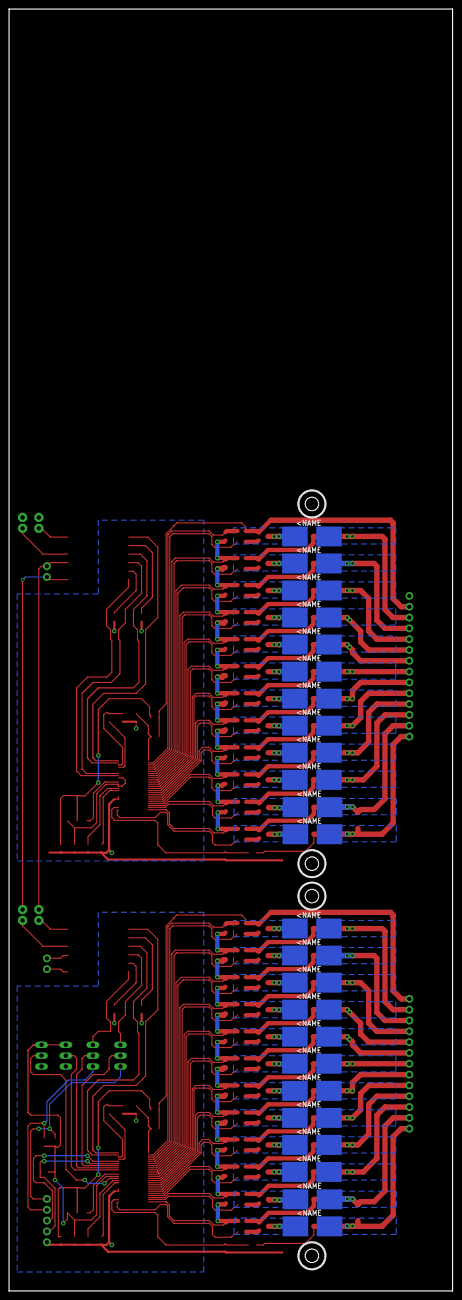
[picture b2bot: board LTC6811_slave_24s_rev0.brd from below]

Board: 2 copper layers, 104.1 x 301.0 mm, 228 parts (24 on the bottom side), 194 nets.

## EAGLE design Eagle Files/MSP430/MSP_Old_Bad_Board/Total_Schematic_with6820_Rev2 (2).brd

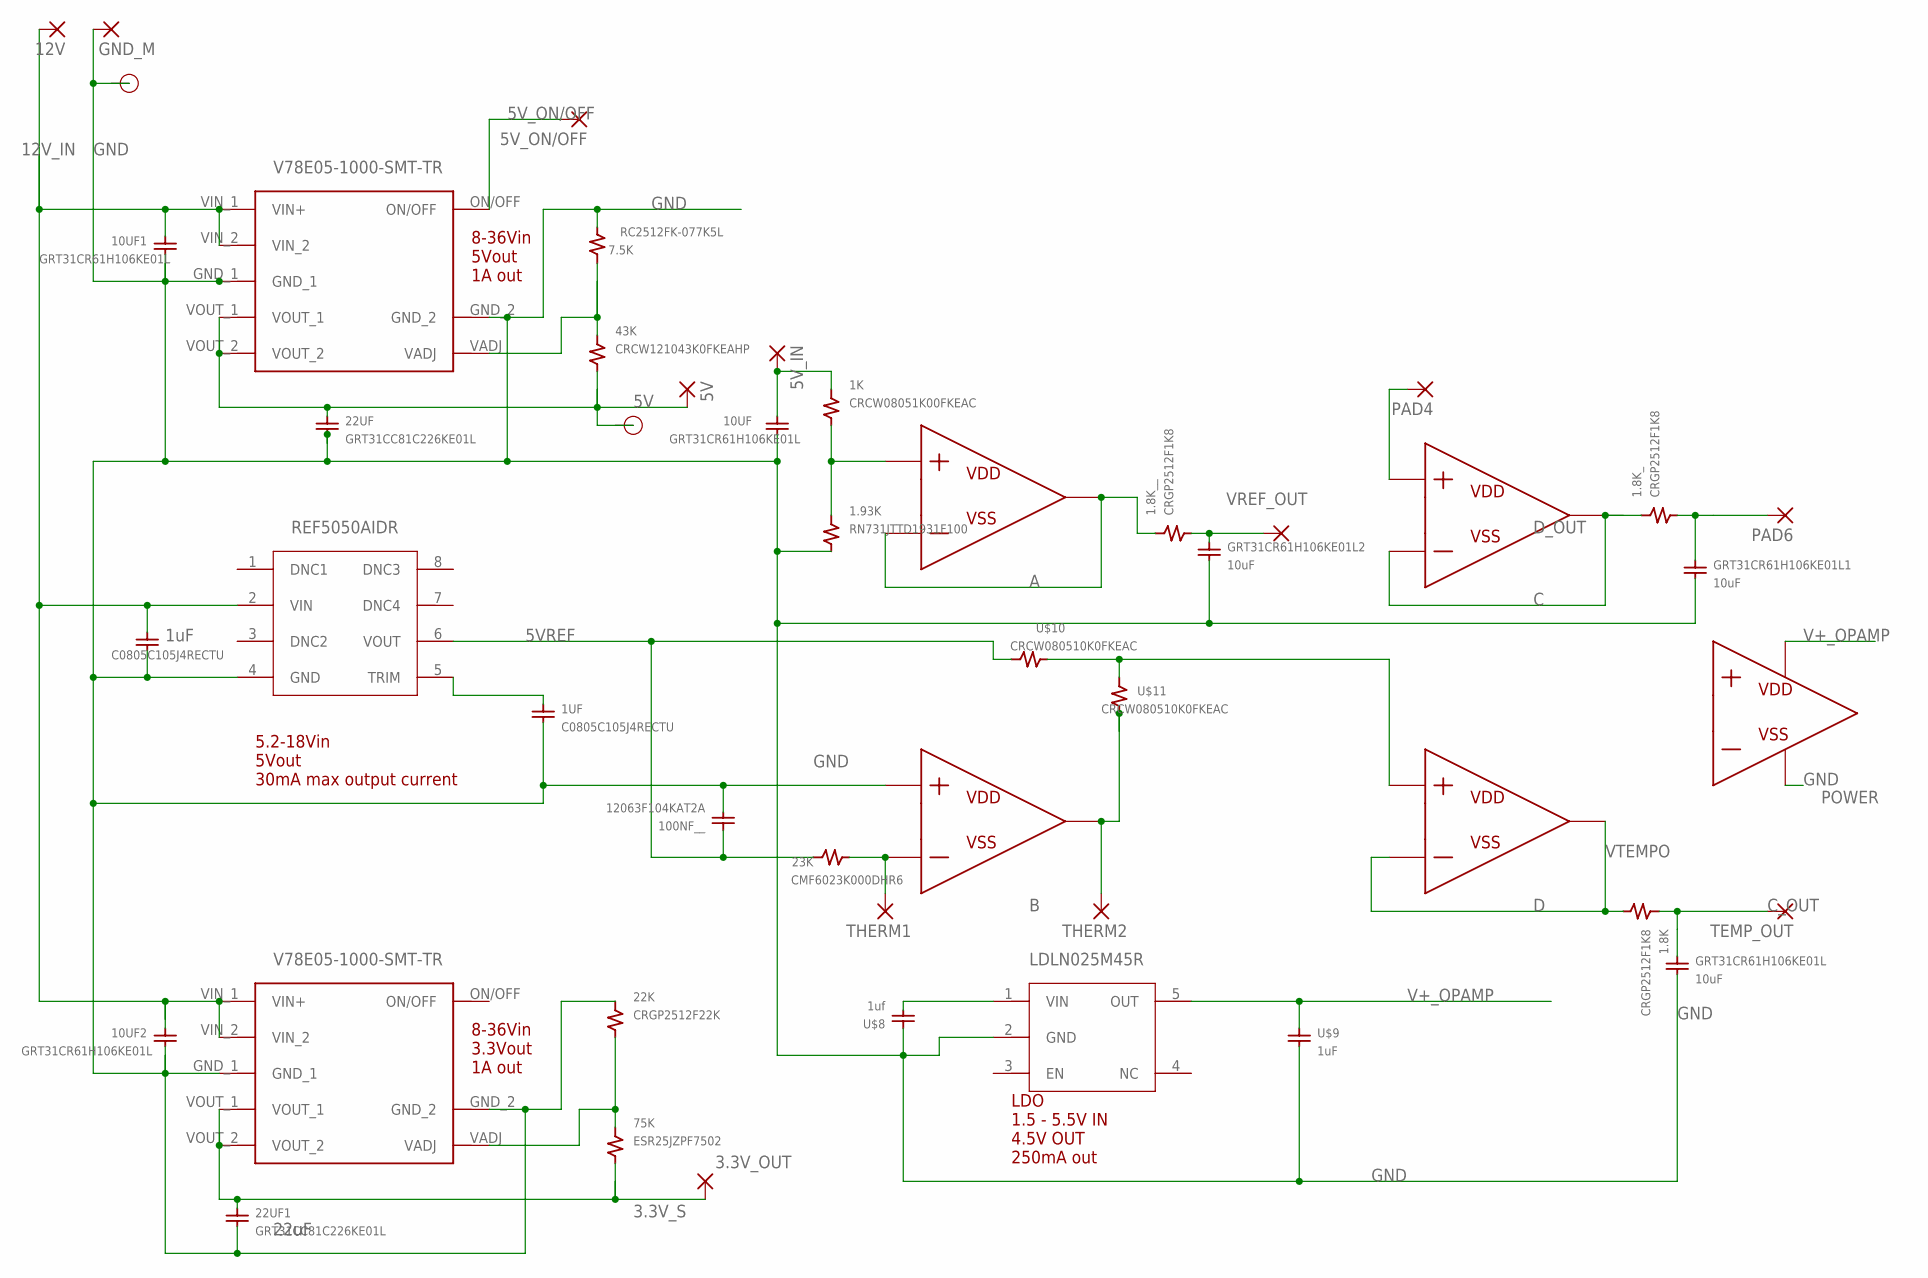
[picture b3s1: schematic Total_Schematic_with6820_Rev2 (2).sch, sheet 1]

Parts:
1.8K, 1.8K_, 1.8K__: CRGP2512F1K8
1.93K: RN731JTTD1931F100
1K: CRCW08051K00FKEAC
1UF: C0805C105J4RECTU
3.3V_OUT, 5V_ON/OFF: 2,15/1,0
5V, 5V_IN, 12V: WIREPAD2,54/1,0; 2,54/1,0
5V_2: HEADER_PIN_2.15/1.0; 2,15/1,0
7.5K: RC2512FK-077K5L
10UF, 10UF1, 10UF2: GRT31CR61H106KE01L
22K: CRGP2512F22K
22UF, 22UF1: GRT31CC81C226KE01L
23K: CMF6023K000DHR6
43K: CRCW121043K0FKEAHP
75K: ESR25JZPF7502
100NF__: 12063F104KAT2A
GND2: HEADER_PIN_2.15/1.0; 2,15/1,0
GND_M: WIREPAD2,54/1,0; 2,54/1,0
GRT31CR61H106KE01L, GRT31CR61H106KE01L1, GRT31CR61H106KE01L2: 10uF; GRT31CR61H106KE01L
PAD4: WIREPAD2,54/1,0; 2,54/1,0
PAD6: 2,15/1,0
TEMP_OUT: 2,15/1,0
THERM1: WIREPAD2,54/1,0; 2,54/1,0
THERM2: 2,15/1,0
U$1: V78E05-SMT-TR; V78E05-1000-SMT-TR
U$2: V78E03-SMT-TR; V78E03-1000-SMT-TR
U$3: REF5050AIDRREF5050AIDR; SO08
U$4: LDLN025M45R
U$5: C0805C105J4RECTU
U$8: 1uf; C0805C105J4RECTU
U$9: 1uF; C0805C105J4RECTU
U$10, U$11: CRCW080510K0FKEAC
U$12: TSV914AIDR
VREF_OUT: 2,15/1,0

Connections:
3.3V_S: 3.3V_OUT.1, 22UF1.2, 75K.P$1, U$2.VOUT_1, U$2.VOUT_2
5V: 5V.1, 5V_2.1, 22UF.2, 43K.1, U$1.VOUT_1, U$1.VOUT_2
5VREF: 23K.2, 100NF__.2, U$3.6 (VOUT), U$10.2
5V_ON/OFF: 5V_ON/OFF.1, U$1.ON/OFF
5V_S: 1K.2, 5V_IN.1, 10UF.2
12V_IN: 10UF1.2, 10UF2.2, 12V.1, U$1.VIN_1 (VIN+), U$1.VIN_2, U$2.VIN_1 (VIN+), U$2.VIN_2, U$3.2 (VIN), U$5.2
C_OUT: 1.8K.2, GRT31CR61H106KE01L.2, TEMP_OUT.1
D_OUT: 1.8K_.1, GRT31CR61H106KE01L1.2, PAD6.1
GND: 1.93K.1, 1UF.1, 7.5K.1, 10UF.1, 10UF1.1, 10UF2.1, 22K.P$2, 22UF.1, 22UF1.1, 100NF__.1, GND2.1, GND_M.1, GRT31CR61H106KE01L.1, GRT31CR61H106KE01L1.1, GRT31CR61H106KE01L2.1, U$1.GND_1, U$1.GND_2, U$2.GND_1, U$2.GND_2, U$3.4 (GND), U$4.2 (GND), U$5.1, U$8.2, U$9.1, U$12.+IN_B, U$12.V- (GND); also elsewhere on the board
unnamed: 1.93K.2, 1K.1, U$12.+IN_A
unnamed: 1.8K_.2, U$12.-IN_C, U$12.OUT_C
unnamed: 7.5K.2, 43K.2, U$1.VADJ
unnamed: 1.8K__.1, GRT31CR61H106KE01L2.2, VREF_OUT.1
unnamed: 22K.P$1, 75K.P$2, U$2.VADJ
unnamed: PAD4.1, U$12.+IN_C
unnamed: 1UF.2, U$3.5 (TRIM)
unnamed: U$10.1, U$11.2, U$12.+IN_D
unnamed: THERM2.1, U$11.1, U$12.OUT_B
unnamed: 23K.1, THERM1.1, U$12.-IN_B
unnamed: U$4.1 (VIN), U$8.1
V+_OPAMP: U$4.5 (OUT), U$9.2, U$12.V+
VREF+: 1.8K__.2, U$12.-IN_A, U$12.OUT_A
VTEMPO: 1.8K.1, U$12.-IN_D, U$12.OUT_D

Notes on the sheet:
22uF
8-36Vin 5Vout 1A out
8-36Vin 3.3Vout 1A out
5.2-18Vin 5Vout 30mA max output current
1uF
LDO 1.5 - 5.5V IN 4.5V OUT 250mA out

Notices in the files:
parts and their libraries:
SparkFun-Connectors: Licensing: Creative Commons ShareAlike 4.0 International - https://creativecommons.org/licenses/by-sa/4.0
